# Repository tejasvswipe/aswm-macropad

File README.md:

# ASWM Macropad

16-key RP2040 macropad with rotary encoder, custom PCB, firmware, and printable enclosure.

[CAD source and STL files](CAD/openscad_design/README.md) · [Firmware](Firmware/README.md) · [Bill of materials](BOM.csv) · [Schematic PDF](PCB/hackpad16_schematic.pdf)

## Gallery

| | | |
|---|---|---|
|  |  |  |
|  |  |  |
|  |  |  |
|  |  |  |
|  |  |  |

## Pin map

| Function | Signals | GPIO |
|---|---|---|
| Display mux optional | SDA / SCL | GPIO8 / GPIO9 |
| Neon lighting | WS2812B data | GPIO4 |
| Rotary encoder | A / B / switch | GPIO5 / GPIO6 / GPIO7 |
| Top keys | SW1 / SW2 | GPIO1 / GPIO2 |
| Mid keys | SW3 / SW4 / SW7 | GPIO42 / GPIO41 / GPIO40 |
| Bottom keys | SW6 / SW8 / SW9 | GPIO39 / GPIO38 / GPIO21 |

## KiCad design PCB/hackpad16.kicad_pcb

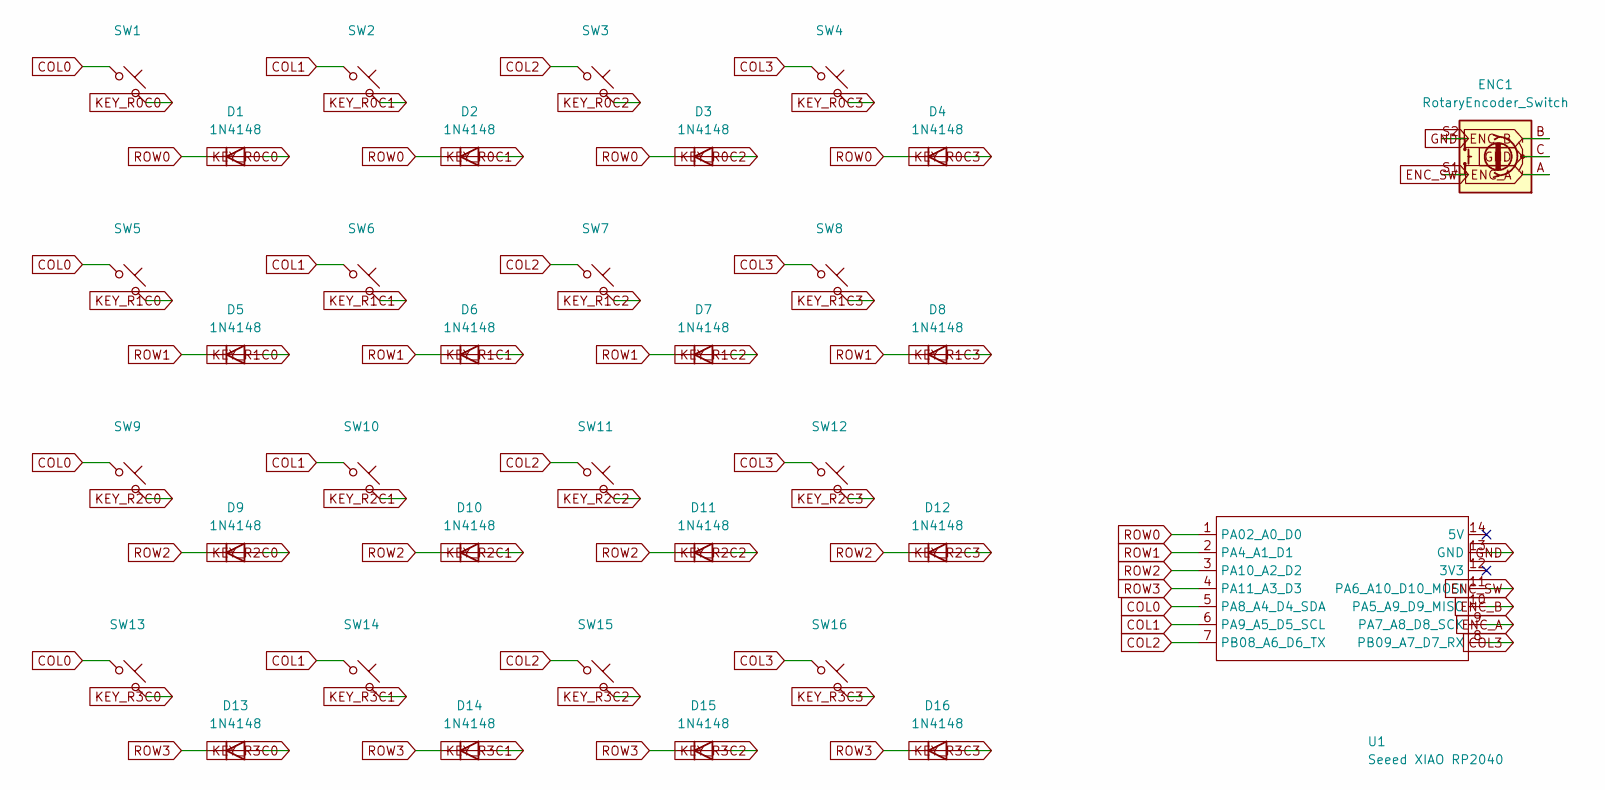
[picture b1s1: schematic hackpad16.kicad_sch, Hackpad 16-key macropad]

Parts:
D1, D2, D3, D4, D5, D6, D7, D8, D9, D10, D11, D12, D13, D14, D15, D16: 1N4148; D_DO-35_SOD27_P7.62mm_Horizontal
ENC1: RotaryEncoder_Switch; RotaryEncoder_Alps_EC11E-Switch_Vertical_H20mm
SW1, SW2, SW3, SW4, SW5, SW6, SW7, SW8, SW9, SW10, SW11, SW12, SW13, SW14, SW15, SW16: SW_Push_45deg; MX-Solderable-1U
U1: Seeed XIAO RP2040; XIAO-Generic-Hybrid-14P-2.54-21X17.8MM

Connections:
COL0: SW1.1, SW5.1, SW9.1, SW13.1, U1.5 (PA8_A4_D4_SDA)
COL1: SW2.1, SW6.1, SW10.1, SW14.1, U1.6 (PA9_A5_D5_SCL)
COL2: SW3.1, SW7.1, SW11.1, SW15.1, U1.7 (PB08_A6_D6_TX)
COL3: SW4.1, SW8.1, SW12.1, SW16.1, U1.8 (PB09_A7_D7_RX)
ENC_A: ENC1.A, U1.9 (PA7_A8_D8_SCK)
ENC_B: ENC1.B, U1.10 (PA5_A9_D9_MISO)
ENC_SW: ENC1.S1, U1.11 (PA6_A10_D10_MOSI)
GND: ENC1.C, ENC1.S2, U1.13 (GND)
KEY_R0C0: D1.2 (A), SW1.2
KEY_R0C1: D2.2 (A), SW2.2
KEY_R0C2: D3.2 (A), SW3.2
KEY_R0C3: D4.2 (A), SW4.2
KEY_R1C0: D5.2 (A), SW5.2
KEY_R1C1: D6.2 (A), SW6.2
KEY_R1C2: D7.2 (A), SW7.2
KEY_R1C3: D8.2 (A), SW8.2
KEY_R2C0: D9.2 (A), SW9.2
KEY_R2C1: D10.2 (A), SW10.2
KEY_R2C2: D11.2 (A), SW11.2
KEY_R2C3: D12.2 (A), SW12.2
KEY_R3C0: D13.2 (A), SW13.2
KEY_R3C1: D14.2 (A), SW14.2
KEY_R3C2: D15.2 (A), SW15.2
KEY_R3C3: D16.2 (A), SW16.2
ROW0: D1.1 (K), D2.1 (K), D3.1 (K), D4.1 (K), U1.1 (PA02_A0_D0)
ROW1: D5.1 (K), D6.1 (K), D7.1 (K), D8.1 (K), U1.2 (PA4_A1_D1)
ROW2: D9.1 (K), D10.1 (K), D11.1 (K), D12.1 (K), U1.3 (PA10_A2_D2)
ROW3: D13.1 (K), D14.1 (K), D15.1 (K), D16.1 (K), U1.4 (PA11_A3_D3)

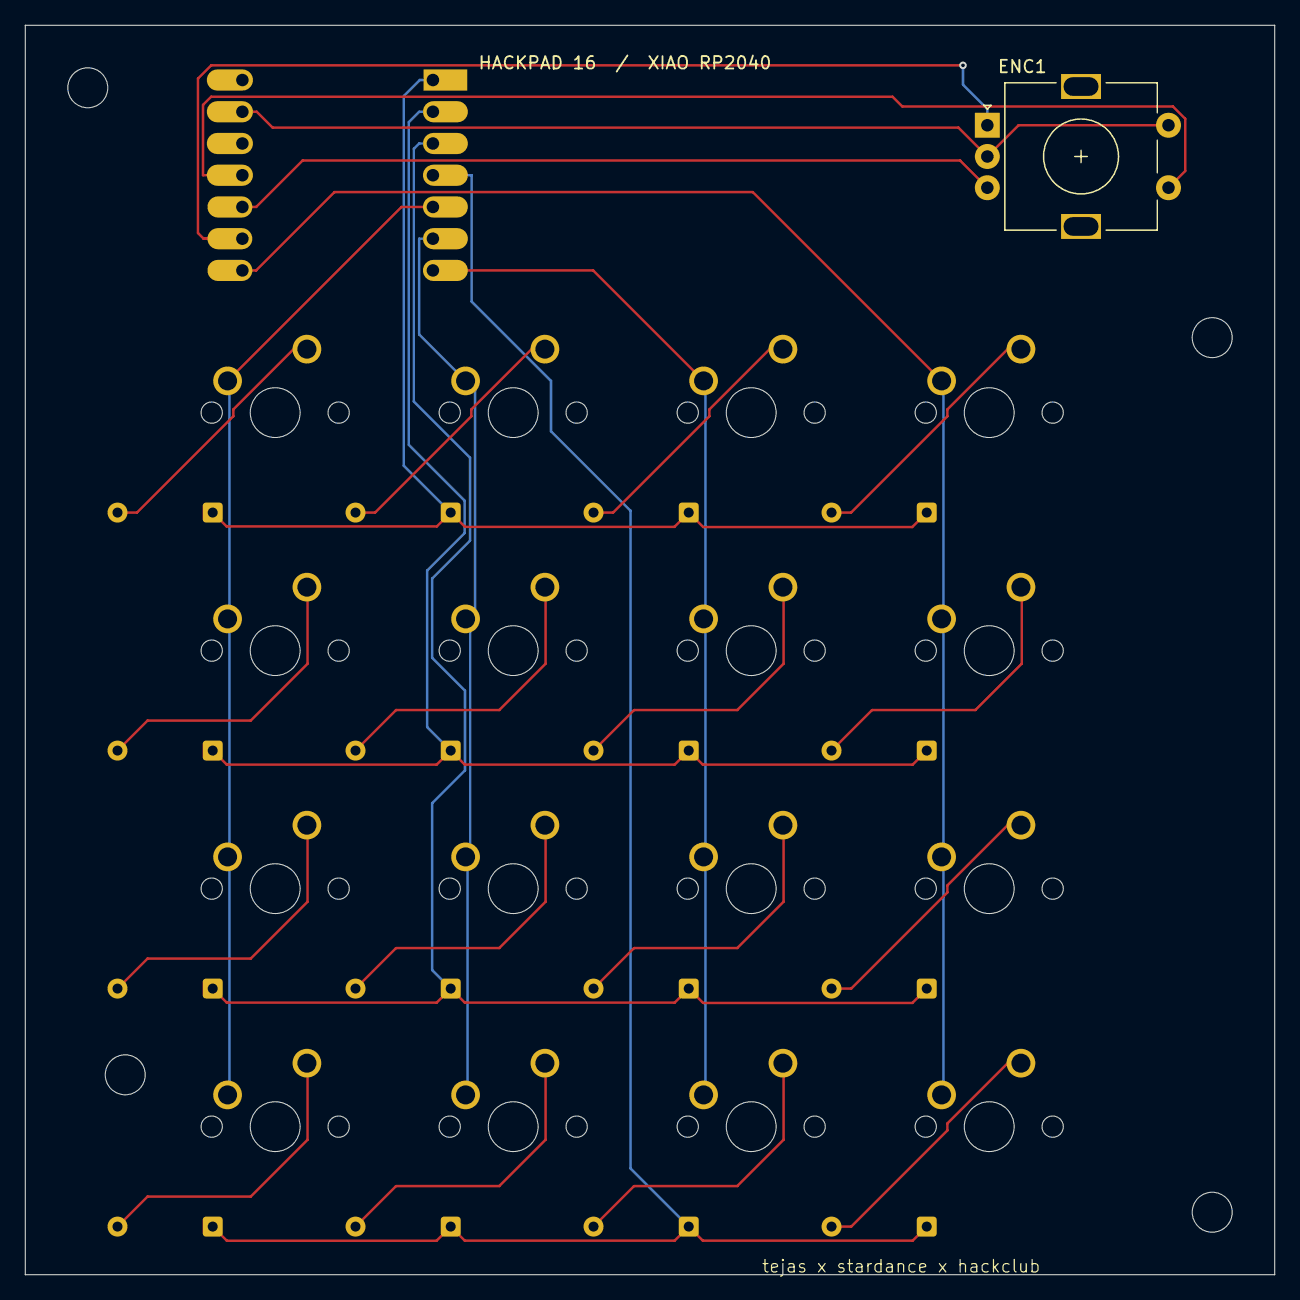
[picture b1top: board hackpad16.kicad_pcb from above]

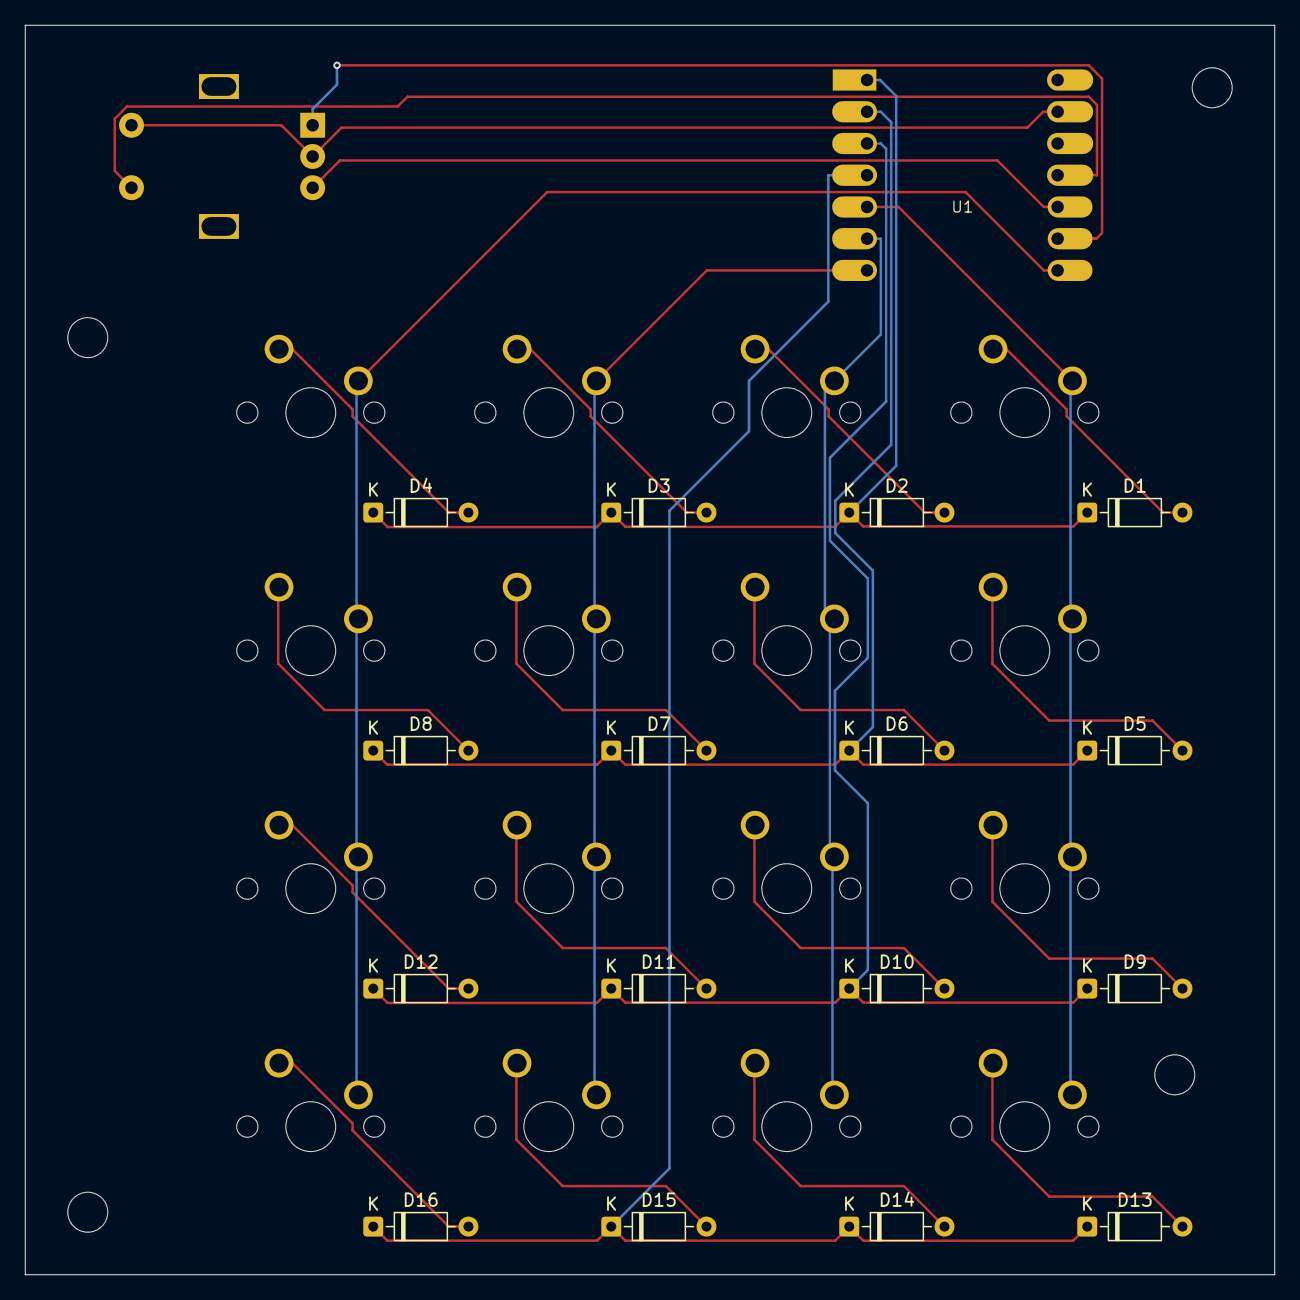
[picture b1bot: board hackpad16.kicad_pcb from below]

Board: 2 copper layers, 100.0 x 100.0 mm, 38 parts (17 on the bottom side), 28 nets.

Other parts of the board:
H1, H2, H3, H4: M3 Mounting Hole; MountingHole_3.2mm_M3

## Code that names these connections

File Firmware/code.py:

import time
import board
import digitalio
import usb_hid
from adafruit_hid.keyboard import Keyboard
from adafruit_hid.keycode import Keycode
from adafruit_hid.consumer_control import ConsumerControl
from adafruit_hid.consumer_control_code import ConsumerControlCode

# KiCad schematic pinout: ROW0..3 = D0..D3, COL0..3 = D4..D7.
ROWS = (board.D0, board.D1, board.D2, board.D3)
COLS = (board.D4, board.D5, board.D6, board.D7)
ENC_A, ENC_B, ENC_SW = board.D8, board.D9, board.D10

keyboard = Keyboard(usb_hid.devices)
consumer = ConsumerControl(usb_hid.devices)

rows = []
for pin in ROWS:
    io = digitalio.DigitalInOut(pin)
    io.direction = digitalio.Direction.INPUT
    io.pull = digitalio.Pull.UP
    rows.append(io)

cols = []
for pin in COLS:
    io = digitalio.DigitalInOut(pin)
    io.direction = digitalio.Direction.OUTPUT
    io.value = True
    cols.append(io)

enc_a = digitalio.DigitalInOut(ENC_A)
enc_a.direction = digitalio.Direction.INPUT
enc_a.pull = digitalio.Pull.UP
enc_b = digitalio.DigitalInOut(ENC_B)
enc_b.direction = digitalio.Direction.INPUT
enc_b.pull = digitalio.Pull.UP
enc_sw = digitalio.DigitalInOut(ENC_SW)
enc_sw.direction = digitalio.Direction.INPUT
enc_sw.pull = digitalio.Pull.UP

# SW1..SW16: copy, paste, Chrome tab controls, then Windows workspaces.
# The matrix is scanned row-major: SW1 = row 0/col 0.
KEYMAP = {
    0: (Keycode.CONTROL, Keycode.C),
    1: (Keycode.CONTROL, Keycode.V),
    2: (Keycode.CONTROL, Keycode.TAB),
    3: (Keycode.CONTROL, Keycode.SHIFT, Keycode.TAB),
    4: (Keycode.CONTROL, Keycode.T),
    5: (Keycode.CONTROL, Keycode.W),
    6: (Keycode.CONTROL, Keycode.L),
    7: (Keycode.GUI, Keycode.ONE),
    8: (Keycode.GUI, Keycode.TWO),
    9: (Keycode.GUI, Keycode.THREE),
    10: (Keycode.GUI, Keycode.FOUR),
    11: (Keycode.GUI, Keycode.FIVE),
    12: (Keycode.GUI, Keycode.SIX),
    13: (Keycode.GUI, Keycode.SEVEN),
    14: (Keycode.GUI, Keycode.EIGHT),
    15: (Keycode.GUI, Keycode.NINE),
}

last_keys = [False] * 16
last_scan = 0
last_encoder = (enc_a.value << 1) | enc_b.value
last_encoder_step = 0
last_encoder_time = 0
last_encoder_switch = True
last_switch_time = 0

# Quadrature transitions. Direction may be reversed by swapping ENC_A/ENC_B.
QUAD = {
    (0, 1): 1, (1, 3): 1, (3, 2): 1, (2, 0): 1,
    (0, 2): -1, (2, 3): -1, (3, 1): -1, (1, 0): -1,
}


def tap(combo):
    for key in combo:
        keyboard.press(key)
    for key in reversed(combo):
        keyboard.release(key)


def scan_keys(now):
    global last_scan
    if now - last_scan < 0.002:
        return
    last_scan = now
    current = [False] * 16
    for col, output in enumerate(cols):
        output.value = False
        time.sleep(0.00015)
        for row, input_pin in enumerate(rows):
            current[row * 4 + col] = not input_pin.value
        output.value = True
    for index, pressed in enumerate(current):
        if pressed and not last_keys[index]:
            tap(KEYMAP[index])
    last_keys[:] = current


def scan_encoder(now):
    global last_encoder, last_encoder_step, last_encoder_time
    state = (enc_a.value << 1) | enc_b.value
    delta = QUAD.get((last_encoder, state), 0)
    last_encoder = state
    if delta:
        last_encoder_step += delta
        if abs(last_encoder_step) >= 4 and now - last_encoder_time > 0.03:
            if last_encoder_step > 0:
                consumer.send(ConsumerControlCode.VOLUME_INCREMENT)
            else:
                consumer.send(ConsumerControlCode.VOLUME_DECREMENT)
            last_encoder_step = 0
            last_encoder_time = now


def scan_encoder_switch(now):
    global last_encoder_switch, last_switch_time
    pressed = not enc_sw.value
    if pressed and last_encoder_switch and now - last_switch_time > 0.18:
        # Works with Spotify and other media players through the OS media key.
        consumer.send(ConsumerControlCode.PLAY_PAUSE)
        last_switch_time = now
    last_encoder_switch = pressed


while True:
    now = time.monotonic()
    scan_keys(now)
    scan_encoder(now)
    scan_encoder_switch(now)
    time.sleep(0.001)
